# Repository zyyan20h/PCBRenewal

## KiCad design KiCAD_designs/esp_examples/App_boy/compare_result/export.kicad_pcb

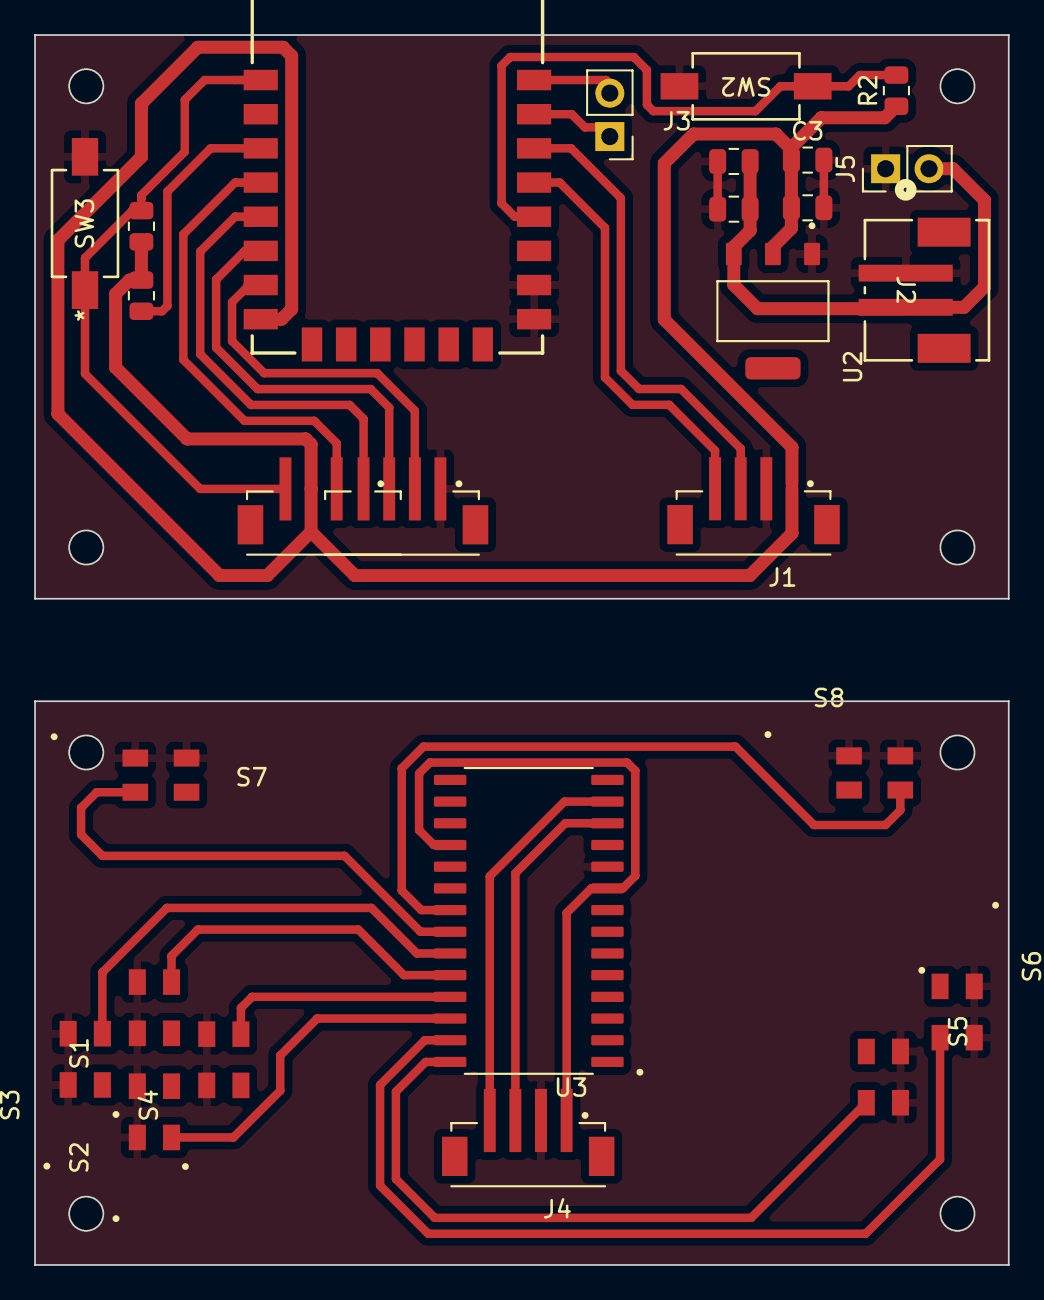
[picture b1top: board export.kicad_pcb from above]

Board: 2 copper layers, 57.0 x 72.0 mm, 26 parts (0 on the bottom side), 24 nets.

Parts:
C1, C2, C3, C4: C; C_0805_2012Metric
J1, J4: B4B-ZR-SM4-TFT_LF__SN_; JST_B4B-ZR-SM4-TFT_LF__SN_
J2: B2B-PH-SM4-TBLFSN; B2B-PH-SM4-TBLFSN_JST
J3, J5: Conn_01x02_Pin; PinHeader_1x02_P2.54mm_Vertical
J6: B7B-ZR-SM4-TFT_LF__SN_; B7B-ZR-SM4-TBLFSN_JST
R1, R2, R4: R; R_0805_2012Metric
S1: up; switch
S2: down; switch
S3: left; switch
S4: right; switch
S5: A; switch
S6: B; switch
S7: RL; switch
S8: RR; switch
SW2, SW3: RS-282G05A3-SM RT; RS-282G05A3-SM RT_CNK
U1: ESP-12F
U2: AMS1117-3.3; SOT229P700X180-4N
U3: MCP23017-E_SO; MCP23017

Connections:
/A: S5.4, U3.28 (GPA7)
/AO: J6.5, U1.4 (GPIO16)
/B: S6.4, U3.27 (GPA6)
/CS: J6.3, U1.6 (GPIO12)
/RL: S7.2, U3.22 (GPA1)
/RR: S8.4, U3.21 (GPA0)
/RST: J6.7, R1.1, SW3.1, U1.1 (RST)
/SCK_mcp: J1.3, J4.3, U1.20 (GPIO5), U3.12 (SCK)
/SCK_screen: J6.2, U1.7 (GPIO13)
/SDA_mcp: J1.4, J4.4, U1.19 (GPIO4), U3.13 (SDA)
/SDA_screen: J6.4, U1.5 (GPIO14)
/VIN: C1.2, C2.2, J2.2, J5.2, U2.3 (VIN)
/boot: R2.2, SW2.1, U1.18 (GPIO0)
/down: S2.2, U3.26 (GPA5)
/left: S3.4, U3.23 (GPA2)
/right: S4.4, U3.25 (GPA4)
/up: S1.4, U3.24 (GPA3)
GND: C1.1, C2.1, C3.2, C4.2, J1.2, J2.1, J4.2, J5.1, J6.1, S1.1, S1.3, S2.1, S2.3, S3.1, S3.3, S4.1, S4.3, S5.1, S5.3, S6.1, S6.3, S7.1, S7.3, S8.1, S8.3, SW2.2, SW3.2, U1.15 (GND), U1.16 (GPIO15), U2.1 (GND/ADJ), U3.10 (VSS)
unnamed: J1.S1 (SHIELD), J1.S2 (SHIELD)
unnamed: J3.1, U1.21 (RXD)
unnamed: J3.2, U1.22 (TXD)
unnamed: J4.S1 (SHIELD), J4.S2 (SHIELD)
unnamed: R4.1, U1.3 (EN)
VCC: C3.1, C4.1, J1.1, J4.1, J6.6, R1.2, R2.1, R4.2, U1.8 (VCC), U2.2 (VOUT), U3.9 (VDD), U3.18 (~RESET)

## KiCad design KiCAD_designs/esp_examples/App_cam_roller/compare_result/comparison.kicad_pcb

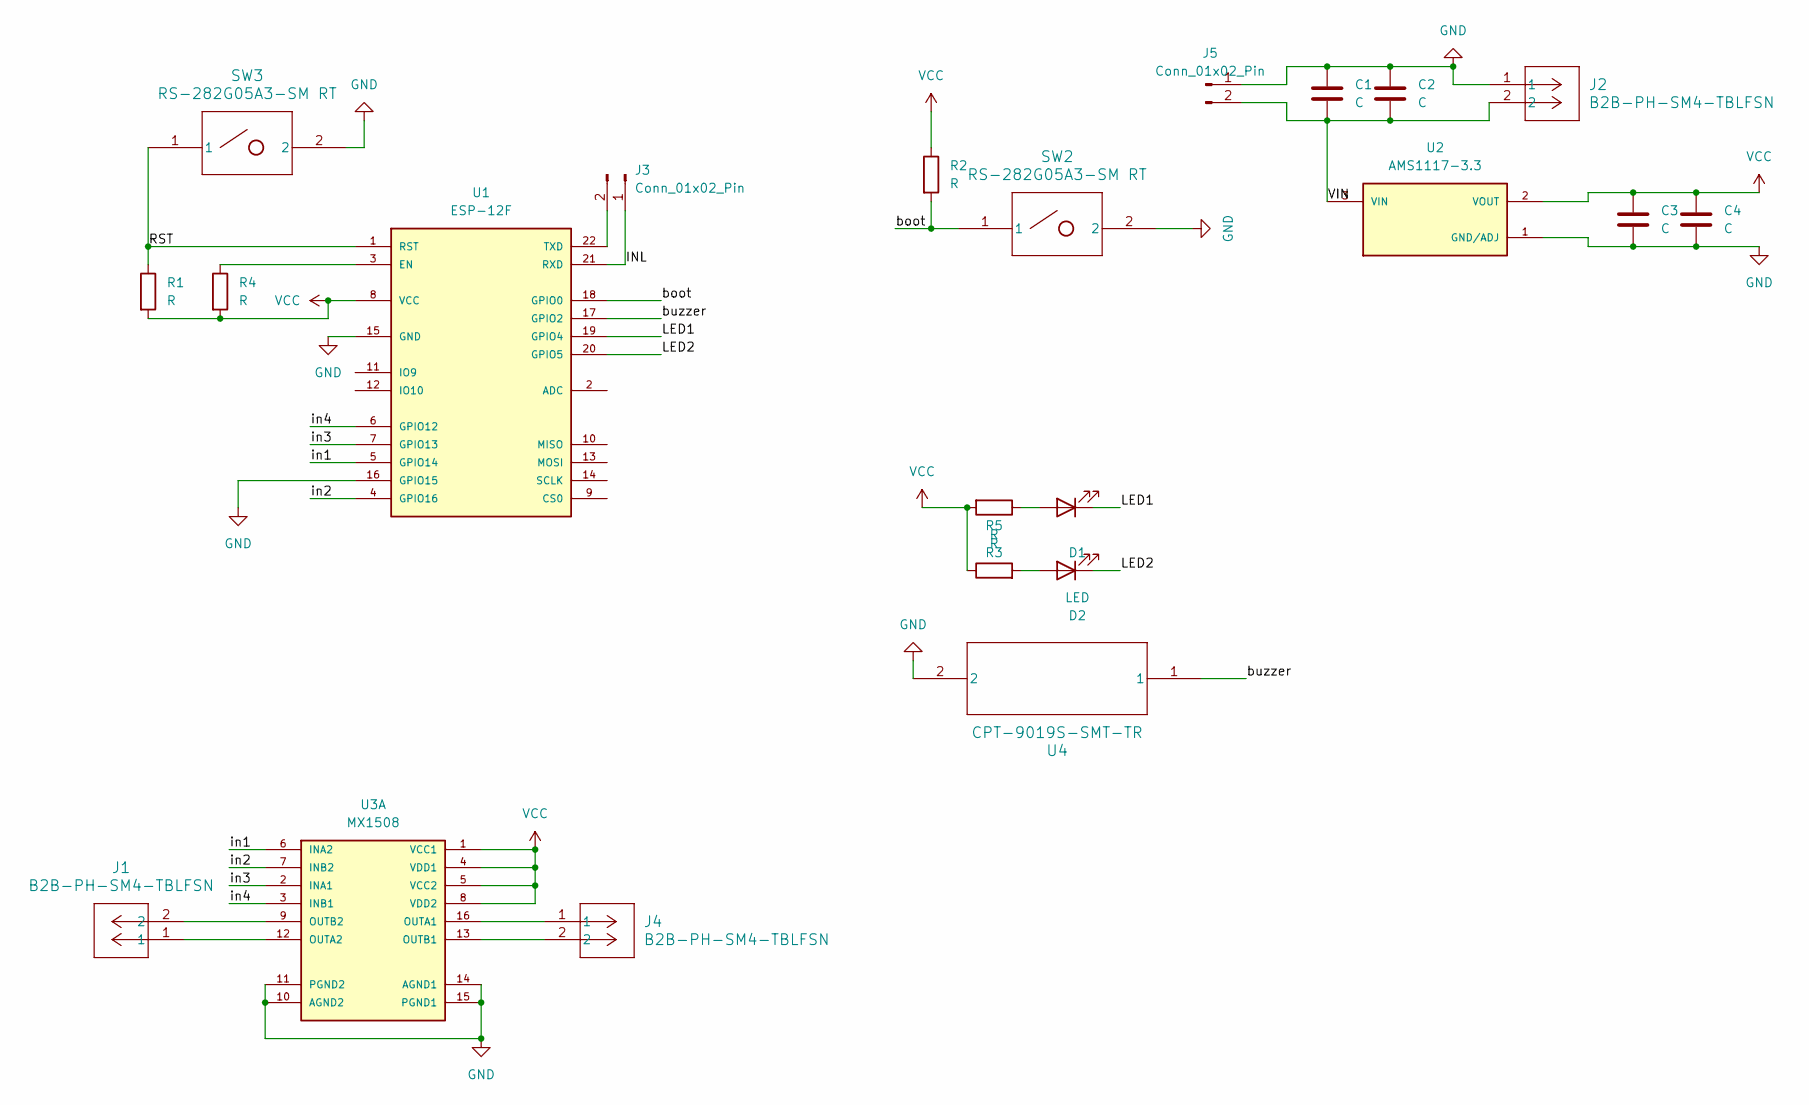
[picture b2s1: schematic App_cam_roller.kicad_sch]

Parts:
C1, C2, C3, C4: C; C_0805_2012Metric
D1, D2: LED; LED_1206_3216Metric
J1, J2, J4: B2B-PH-SM4-TBLFSN; B2B-PH-SM4-TBLFSN_JST
J3, J5: Conn_01x02_Pin; PinHeader_1x02_P2.54mm_Vertical
R1, R2, R3, R4, R5: R; R_0805_2012Metric
SW2, SW3: RS-282G05A3-SM RT; RS-282G05A3-SM RT_CNK
U1: ESP-12F
U2: AMS1117-3.3; SOT229P700X180-4N
U3: MX1508
U4: CPT-9019S-SMT-TR; SM_CPT_9X9_CUD

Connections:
/INL: J3.1, U1.21 (RXD)
/LED1: D1.1 (K), U1.19 (GPIO4)
/LED2: D2.1 (K), U1.20 (GPIO5)
/RST: R1.1, SW3.1, U1.1 (RST)
/VIN: C1.2, C2.2, J2.2, J5.2, U2.3 (VIN)
/boot: R2.2, SW2.1, U1.18 (GPIO0)
/buzzer: U1.17 (GPIO2), U4.1
/in1: U1.5 (GPIO14), U3.6 (INA2)
/in2: U1.4 (GPIO16), U3.7 (INB2)
/in3: U1.7 (GPIO13), U3.2 (INA1)
/in4: U1.6 (GPIO12), U3.3 (INB1)
GND: C1.1, C2.1, C3.2, C4.2, J2.1, J5.1, SW2.2, SW3.2, U1.15 (GND), U1.16 (GPIO15), U2.1 (GND/ADJ), U3.10 (AGND2), U3.11 (PGND2), U3.14 (AGND1), U3.15 (PGND1), U4.2
unnamed: D1.2 (A), R3.1
unnamed: D2.2 (A), R5.2
unnamed: J3.2, U1.22 (TXD)
unnamed: R4.1, U1.3 (EN)
unnamed: J4.1, U3.16 (OUTA1)
unnamed: J1.1, U3.12 (OUTA2)
unnamed: J4.2, U3.13 (OUTB1)
unnamed: J1.2, U3.9 (OUTB2)
VCC: C3.1, C4.1, R1.2, R2.1, R3.2, R4.2, R5.1, U1.8 (VCC), U2.2 (VOUT), U3.1 (VCC1), U3.4 (VDD1), U3.5 (VCC2), U3.8 (VDD2)

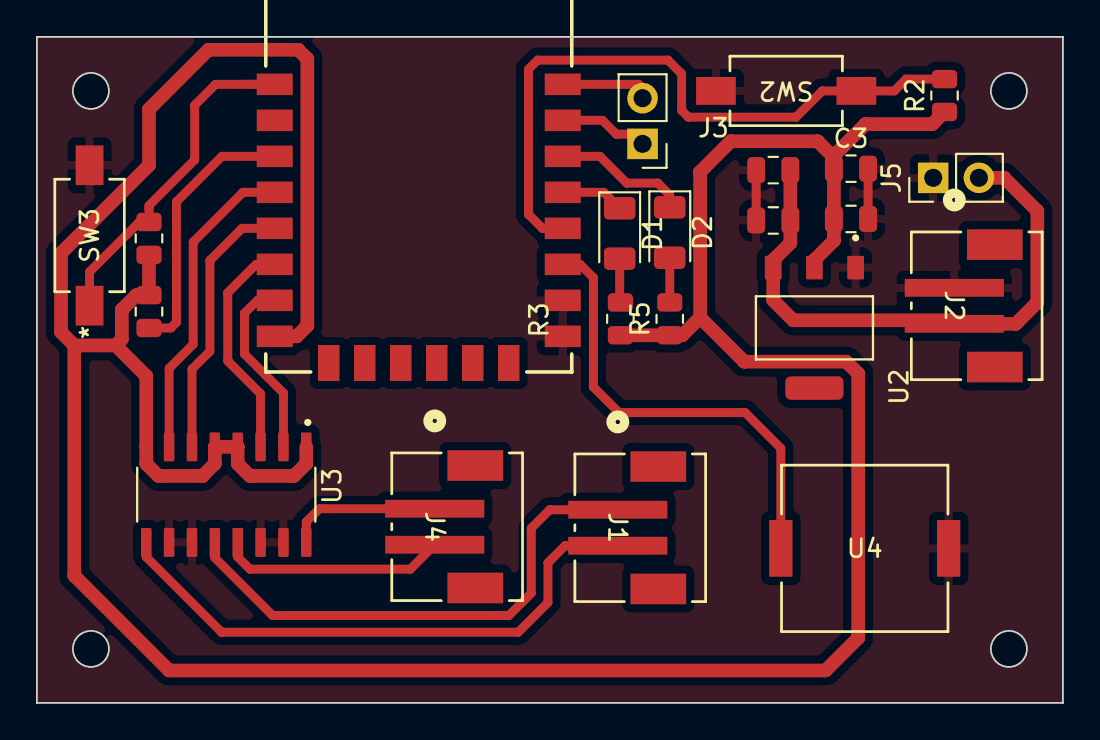
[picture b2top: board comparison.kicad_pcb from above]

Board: 2 copper layers, 57.0 x 37.0 mm, 22 parts (0 on the bottom side), 21 nets.

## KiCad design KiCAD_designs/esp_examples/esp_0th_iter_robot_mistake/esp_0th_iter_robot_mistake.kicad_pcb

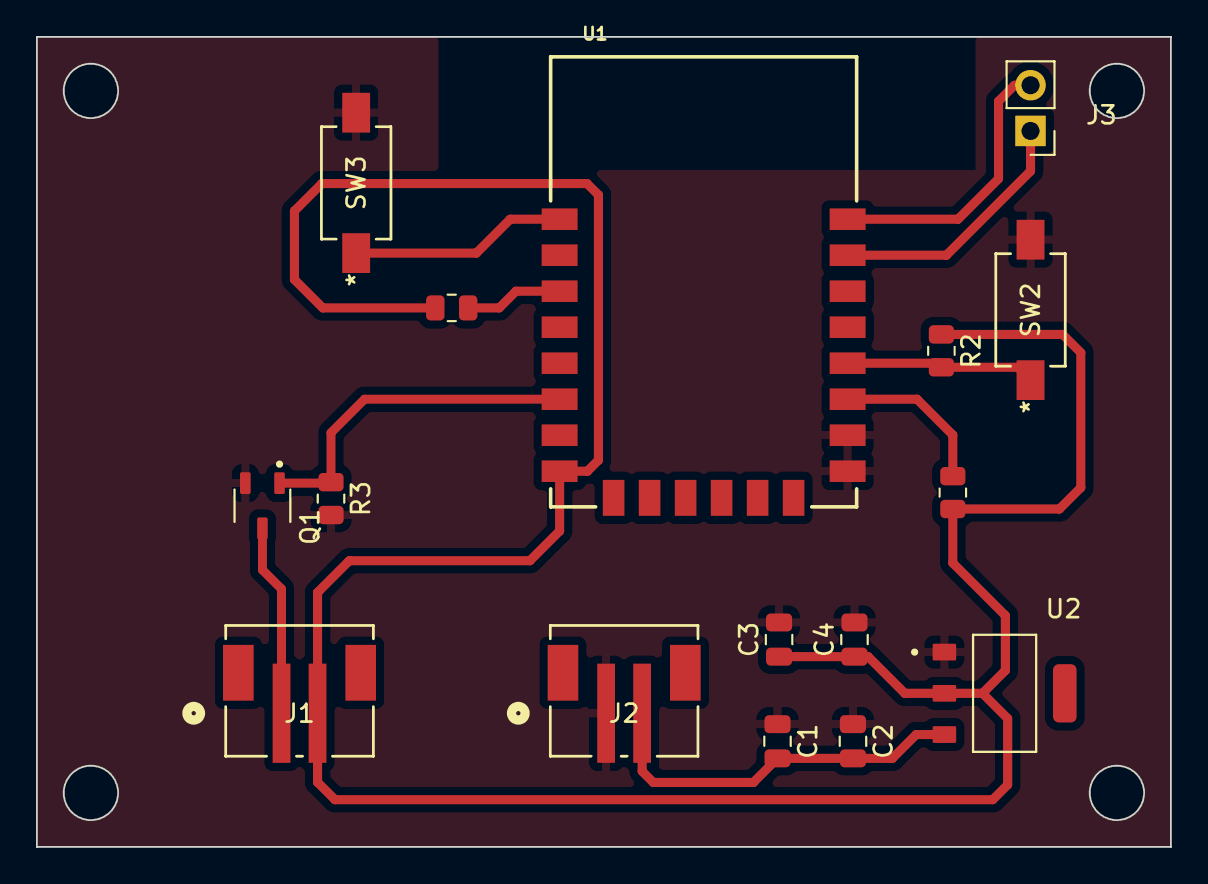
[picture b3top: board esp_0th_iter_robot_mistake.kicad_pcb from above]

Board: 2 copper layers, 63.0 x 45.0 mm, 16 parts (0 on the bottom side), 11 nets.

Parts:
C1, C2, C3, C4: C; C_0805_2012Metric
J1, J2: B2B-PH-SM4-TBLFSN; CONN_B2B-PH-SM4-TBLFSN_JST
J3: Conn_01x02_Pin; PinHeader_1x02_P2.54mm_Vertical
Q1: AO3400A; SOT95P280X125-3N
R2, R3, R4, R6: R; R_0805_2012Metric
SW2, SW3: RS-282G05A3-SM RT; RS-282G05A3-SM RT_CNK
U1: ESP-12F
U2: AMS1117-3.3; SOT229P700X180-4N

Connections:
/DC: Q1.1, R3.1, U1.6 (GPIO12)
/boot: R2.2, SW2.1, U1.18 (GPIO0)
/servo: R6.1, U1.17 (GPIO2)
GND: C1.1, C2.1, C3.2, C4.2, J2.1, Q1.2, R3.2, SW2.2, SW3.2, U1.15 (GND), U1.16 (GPIO15), U2.1 (GND/ADJ)
unnamed: J1.1, Q1.3
unnamed: J3.1, U1.21 (RXD)
unnamed: J3.2, U1.22 (TXD)
unnamed: R4.1, U1.3 (EN)
unnamed: SW3.1, U1.1 (RST)
unnamed: C1.2, C2.2, J2.2, U2.3 (VIN)
VCC: C3.1, C4.1, J1.2, R2.1, R4.2, R6.2, U1.8 (VCC), U2.2 (VOUT)

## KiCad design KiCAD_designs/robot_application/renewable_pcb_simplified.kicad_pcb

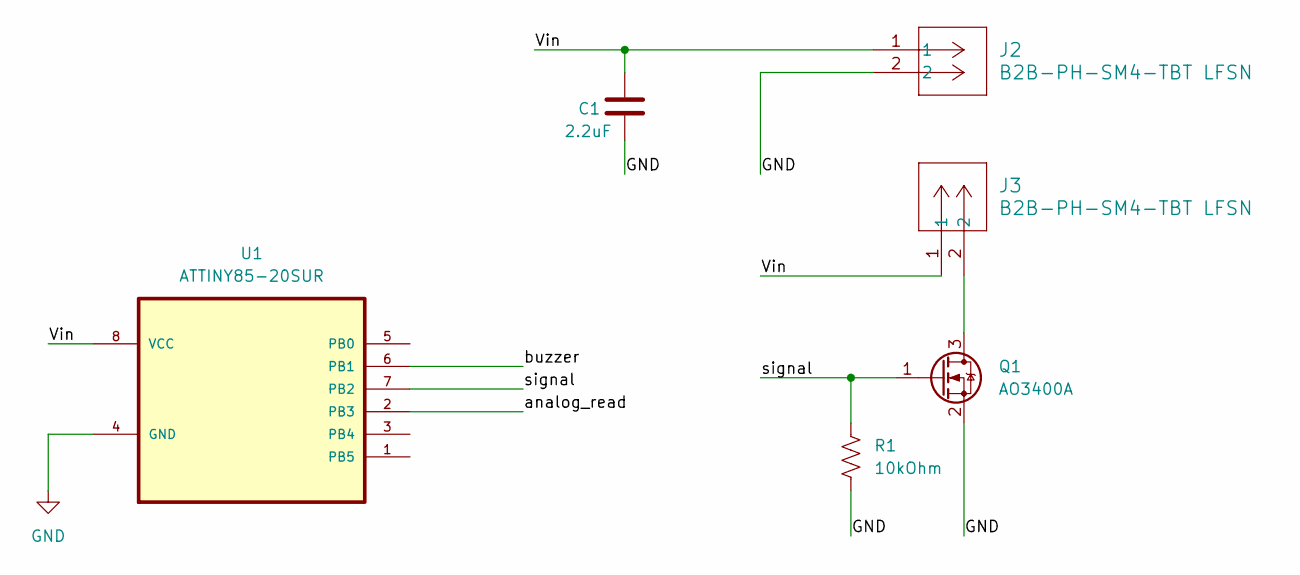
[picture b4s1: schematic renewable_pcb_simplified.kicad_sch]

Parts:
C1: 2.2uF; C_0805_2012Metric
J2, J3: B2B-PH-SM4-TBT LFSN; CONN2_B2B-PH-SM4_JST
Q1: AO3400A; SOT-23-3
R1: 10kOhm; R_0805_2012Metric
U1: ATTINY85-20SUR; MPN ATTINY85-20SUR

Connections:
/Vin: C1.1, J2.1, J3.1, U1.8 (VCC)
/analog_read: U1.2 (PB3)
/buzzer: U1.6 (PB1)
/signal: Q1.1 (G), R1.1, U1.7 (PB2)
GND: C1.2, J2.2, Q1.2 (S), R1.2, U1.4 (GND)
unnamed: J3.2, Q1.3 (D)

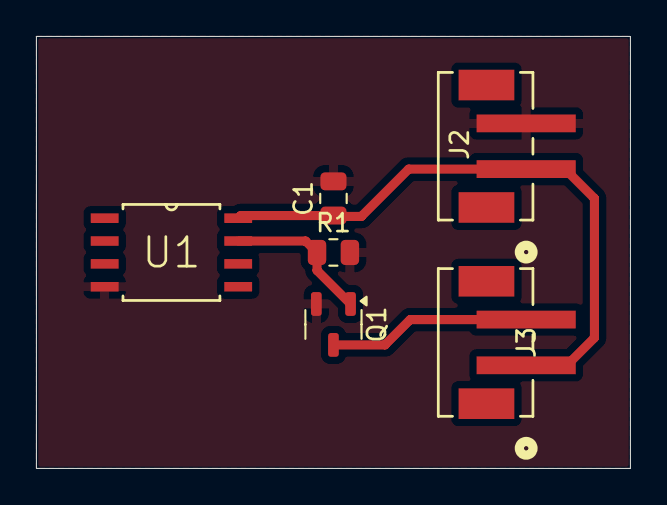
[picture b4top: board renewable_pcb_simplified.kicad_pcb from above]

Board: 2 copper layers, 33.0 x 24.0 mm, 6 parts (0 on the bottom side), 4 nets.
